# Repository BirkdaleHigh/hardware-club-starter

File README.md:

# Hardware Club
### Wednesday After School
### 3:10pm to 4pm, IT Room U5

Learn programming with basic hardware to control lights and motors.  We currently have room for a maximum of 10 people and there's around 5 spots still going. Currently this club is open for year 9 and up to join in. 

Starting next academic year there will be more spots available and a re-cap so anything won't be missed.

# Equipment

For this club we've got a number of [ARDX Start Kits](http://oomlout.co.uk/products/arduino-starter-kit-ardx) complete with [Arduino Uno](http://oomlout.co.uk/collections/arduino/products/arduino-uno) boards. Using these boards you will complete the projects listed below and then go on to create whatever you want.

It is not necessary to purchase this equipment. Links are provided purely for information.

You are welcome to bring your own equipment but it is your responsibility to keep it safe.

# Projects

## 0. Circuits and software [\[View\]](AltBlink/)

With this project you'll start with zero programming or circuits  knowledge and learn to;

* wire a LED array
* use variables
* create your own function
* use parameters

[\[Full Project\]](AltBlink/)

## 1. Robot Driving Lesson [\[View\]](RobotController/)

With an Arduino we will DIY our own brain to drive the [Big Trak Rovers](http://rover.bigtrakxtr.co.uk/what.html) around a course. This is the first step on a path to making hardware work for you.

With the skills gained from getting started with project zero reverse engineer how these robots are controlled and do it yourself better than the creators. You'll want to master functions,  parameters and variables to make life easy here.

You will finish this project with an understanding of how to learn something you don't have any idea to do in the first place.

[\[Full Project\]](RobotController/)

## 2. Serially Working [\[View\]](Serially/)

The plan is loosely:

* Serial Talking, uses the serial monitor to accept input and perform logic with a  response. 
* Temperature Sensor, analogue input and the serial monitor
* Light Sensor, repeat analogue input and serial monitor.
* Potentiometer, input with analogue and debugging with the serial monitor
* Servo Motor, Move positions with an analogue output.

[\[Full Project\]](Serially/)

## 3. Hardware Technique

Examples that show you using programming techniques to make using hardware simple to you.
These can be further built upon with your own ideas.

* *[Servo](servo/) chaning the input position to an output value, reading over the serial port.

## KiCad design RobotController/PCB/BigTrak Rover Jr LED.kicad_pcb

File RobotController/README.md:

# BigTrak Rover Jr.

Make your own brains the to BigTrak Rover with a simple LED array and microcontroller. This replaces using a phone in the clamp.

## Parts

- Controller (Arduino in this case)
- x4 LEDs
- x4 matching resistors (560ohm)
- Some wires and connectors or soldering supplies. (Or included PCB)
- Something to insulate the wires from each other. Tape or surplus over sized wire you can strip. (Old electrical cable in this case)

## How

The BigTrak Rover is controlled by 4 light-sensitive diodes in a row. Exposing these to light in a specific order controls which motors are powered and the direction. Duration is controlled by the time the diode is lit.

The app works by holding a phone in a specific place that lights the screen in a specific order for the diodes.

This project will replace the phone.

We need something to hold 4 LEDs in place in front of the diodes and **also to press down on the power switch at the base of the phone clamp**.

## Control

Now we know how the rover works we need to create our prototype to prove the idea. So we need 4 LEDs wired up to you controller now, perfect time to get the breadboard out.

The logic we need do make the LEDs display is as [seen from the working out](logic_chart.jpg) photo.

Cleaned up looks like;

|   1   |   2   |   3   |   4   |               |
| :---: | :---: | :---: | :---: | ------------- |
|       |   x   |   x   |       | **forward**   |
|       |       |   x   |   x   | **left**      |
|   x   |   x   |       |       | **right**     |
|   x   |       |       |   x   | **reverse**\* |

\* The Big Trak app they give you for your phone doesn't actually have reverse. We found this by experimenting.

## Programming
Once you've made a sequence of lights to move the robot, Try making a sequence that can repeat the robots motion so it finishes where it started and loops forever. You'll run into some interesting control problems to thing about

further areas to program might be if you can blink the lights very quickly as a form of speed control.

### Fancy Terms
This first programming you want to do is abstract setting pin number values in sequence making an interface you can read/call easily.
Next you're going to explore are problems using an algorithm with an open control loop system.

## Measurements

There is an SLT and the source SketchUp template for a mounting plate included.
Below lists the measurements used to create those.
The template cuts the control board from the waste in the middle of the mounting board.
Use the small excess rectangles that are cut out to pad the control boards width for the clamp.

### Control Board
Corrugated card the thicker the better to clamp down. 65mm width by 40mm* height.
Place the tip of the LEDs 20mm up from the bottom of the card relative to the clamp.
Space the LED tips 12.5mm apart starting 15mm from one edge of the board.

| Desc. | width | height | offset from bottom |
| ----- | ----- | ------ | ------------------ |
| Size  | 65mm  | 40mm\* |                    |
| LED 1 |       |        | 20mm               |
| LED 2 |       |        | 20mm               |
| LED 3 |       |        | 20mm               |
| LED 4 |       |        | 20mm               |

\* This is a minimum height for the top of the clamp to reach the bottom power switches.

We should end up with something that looks a bit like; 

I hope yours turns out neater. The LED legs were insulated after taking this picture. Make sure yours can't short out when moved around.

### Control Board PCB (Printed Circuit Board)

In the PCB folder is a KiCad project which makes a suitable PCB of the above measurements with SMD (Surface Mount Device, as opposed the through hole like above) components.

This can be made to order reasonably cheaply but it's fiddly if you place components yourself and 3mm x 2mm squares may not be appropriate for children in a club. If you do please consider making a pull request adding to [the real world log](PCB/Manufacture.log)

### Mounting Board (optional)

Mounting board is a rectangle to hold the Arduino and servo to the robot. It's not required to get started. There is a SketchUp mount.skp included which has the all the dimensions useful, we ran ours off on with a laser cutter and 3mm ply wood.
Place all the cut-outs centrally but relative to the front of the mounting board.

| Desc.                  | width | height | offset from front |
| ---------------------- | ----- | ------ | ----------------- |
| Size                   | 100mm | 155mm  | n/a               |
| Central Cutout         | 75mm  | 32mm   | 38mm              |
| Clamp access           | 20mm  | 40mm   | 80mm              |
| Servo Cutout           | 19mm  | 25mm   | 6mm               |
| Arduino mounting holes |       |        |                   |

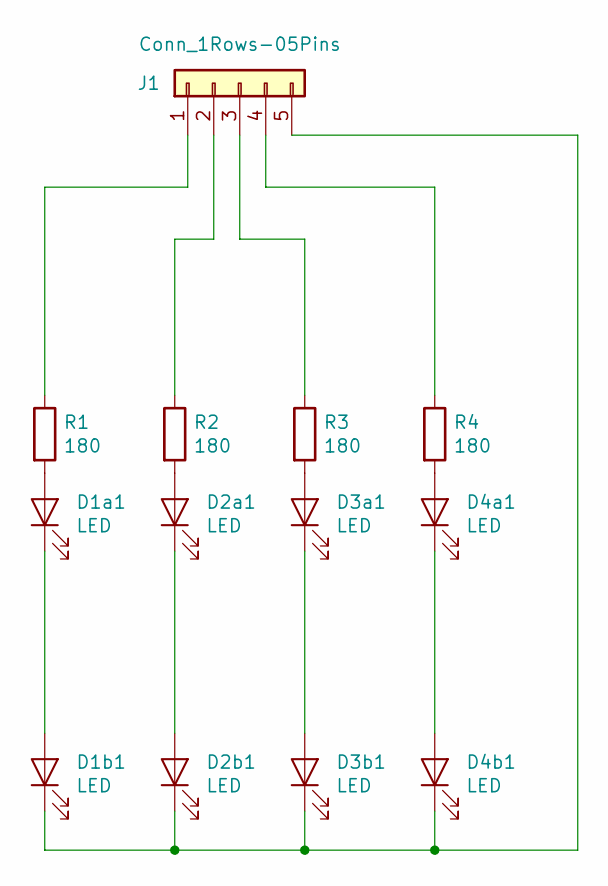
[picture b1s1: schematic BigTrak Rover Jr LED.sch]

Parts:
D1a1, D1b1, D2a1, D2b1, D3a1, D3b1, D4a1, D4b1: LED; LED_1206_3216Metric_Pad1.42x1.75mm_HandSolder
J1: Conn_1Rows-05Pins; PinHeader_1x05_P2.54mm_Vertical
R1, R2, R3, R4: 180; R_1206_3216Metric_Pad1.42x1.75mm_HandSolder

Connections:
unnamed: D1a1.1 (K), D1b1.2 (A)
unnamed: D1a1.2 (A), R1.2
unnamed: D1b1.1 (K), D2b1.1 (K), D3b1.1 (K), D4b1.1 (K), J1.5
unnamed: D2a1.1 (K), D2b1.2 (A)
unnamed: D2a1.2 (A), R2.2
unnamed: D3a1.1 (K), D3b1.2 (A)
unnamed: D3a1.2 (A), R3.2
unnamed: D4a1.1 (K), D4b1.2 (A)
unnamed: D4a1.2 (A), R4.2
unnamed: J1.1, R1.1
unnamed: J1.2, R2.1
unnamed: J1.3, R3.1
unnamed: J1.4, R4.1

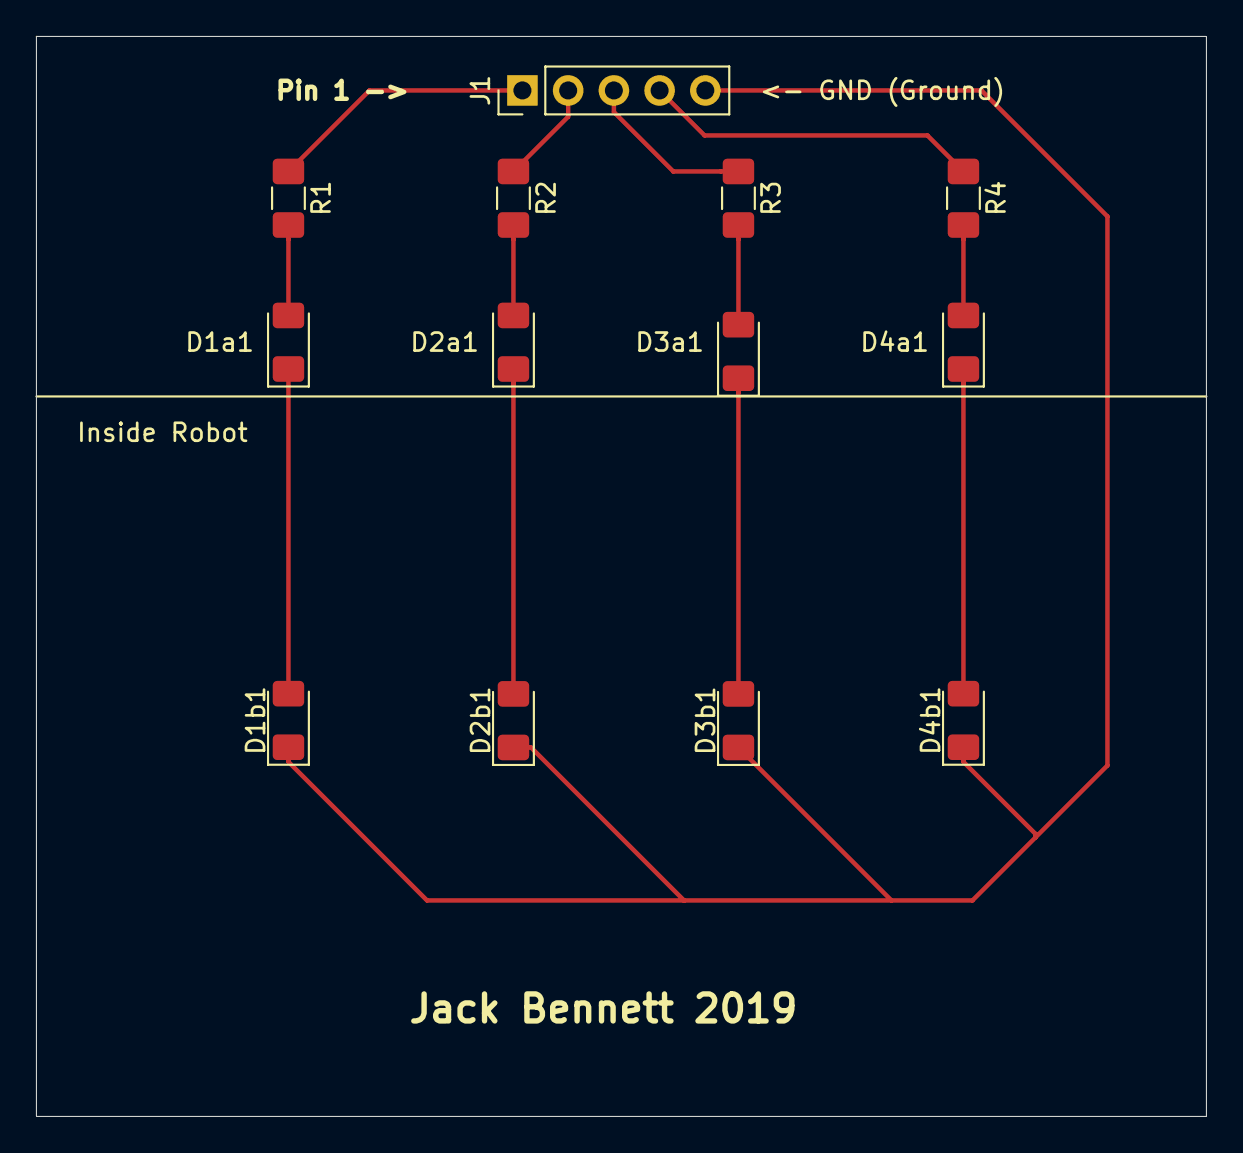
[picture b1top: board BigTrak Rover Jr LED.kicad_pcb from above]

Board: 2 copper layers, 65.0 x 60.0 mm, 13 parts (0 on the bottom side), 13 nets.

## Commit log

2015-06-23 Starter project file of programming concepts
    Using hardware LEDs to demonstrate variables and state.
    A file of things to learn from the script to gain an understanding.
2015-06-24 Starter Project example
    As this club is to learn programming, Take a long look at the example
    here. It uses lots of concepts and requires an understading of state and
    logic.
2015-07-01 Improve documentation
    Rename logic diagram to avoid confusion with future circuit diagrams
    Add an image of the comeplete project
2015-09-14 Project 1. Robot Driving
2015-09-17 Describe the project in detail
    Adding enough infromation for someone to recreate the project without
    needing to be present in the club.
2015-09-17 Relative links to subfolder project in README
2015-09-17 Add a project to get over the basics
2015-10-14 Basic echo program with the serial port
    The serial port is a method to pass messages between the computer
    attacheed to the arduino and the arduino itself.
    This is the bare minimum to see you messages in the serial monitor.
2015-10-14 Teset for a message we expect
    If we don't get the message expected then just echo back the input.
    We've had to account for the message variable being set to the last data
    that was sent to the board here after a message has already been written.
2015-10-14 Speed up the responce to messages
    Reading the arduino.cc reference for the Serial library we find a function
    called setTimeout which appears to be exactly what we want.
2015-11-18 Serial port control and analogue data
    Add tasks to complete for using a serial port to communicate with the
    arduino.
2015-11-19 Add a section to the intro project to explain some the breadboard.
    correcting some minor typos and bad english.
2016-10-13 New CAD Model of the mounting plate
2016-10-13 Add LED insert template into mount plate waste cutout
    Adjust the mountplate clamp opening size to avoid rocking on the top of
    the robot.
    Added the mounting pattern for the LED insert board in the waste cutout
    from the mount template
2016-10-13 Update readme to describe the mount template
2016-10-13 Ignore certain files from version control
2019-09-25 Toning down the pun a notch
2019-09-25 Add PCB to RobotController Section, Docs improvements
    There's a KiCad PCB added to the project that's ready to have made
    should you not want to make a card version for the LEDs.
2019-10-09 Add image of the produced v1 PCB
2019-10-18 Starting topic 3 for re-usable examples
2019-11-04 Include a basic example to cover in lesson 0, validating setup.
2019-11-09 Add costs to Manufacture log for reference.
2019-11-11 Advanced LED Test display example for the board
2019-11-12 Add a diagram of how to wire motor controllers
2019-11-21 Add a examples folder for general demo files.
2019-12-02 including some student work as an example of progress
